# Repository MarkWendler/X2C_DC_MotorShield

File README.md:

# X2C_DC_MotorShield
DC motor driver expansion board for X2C+ development board. [Hardware project]

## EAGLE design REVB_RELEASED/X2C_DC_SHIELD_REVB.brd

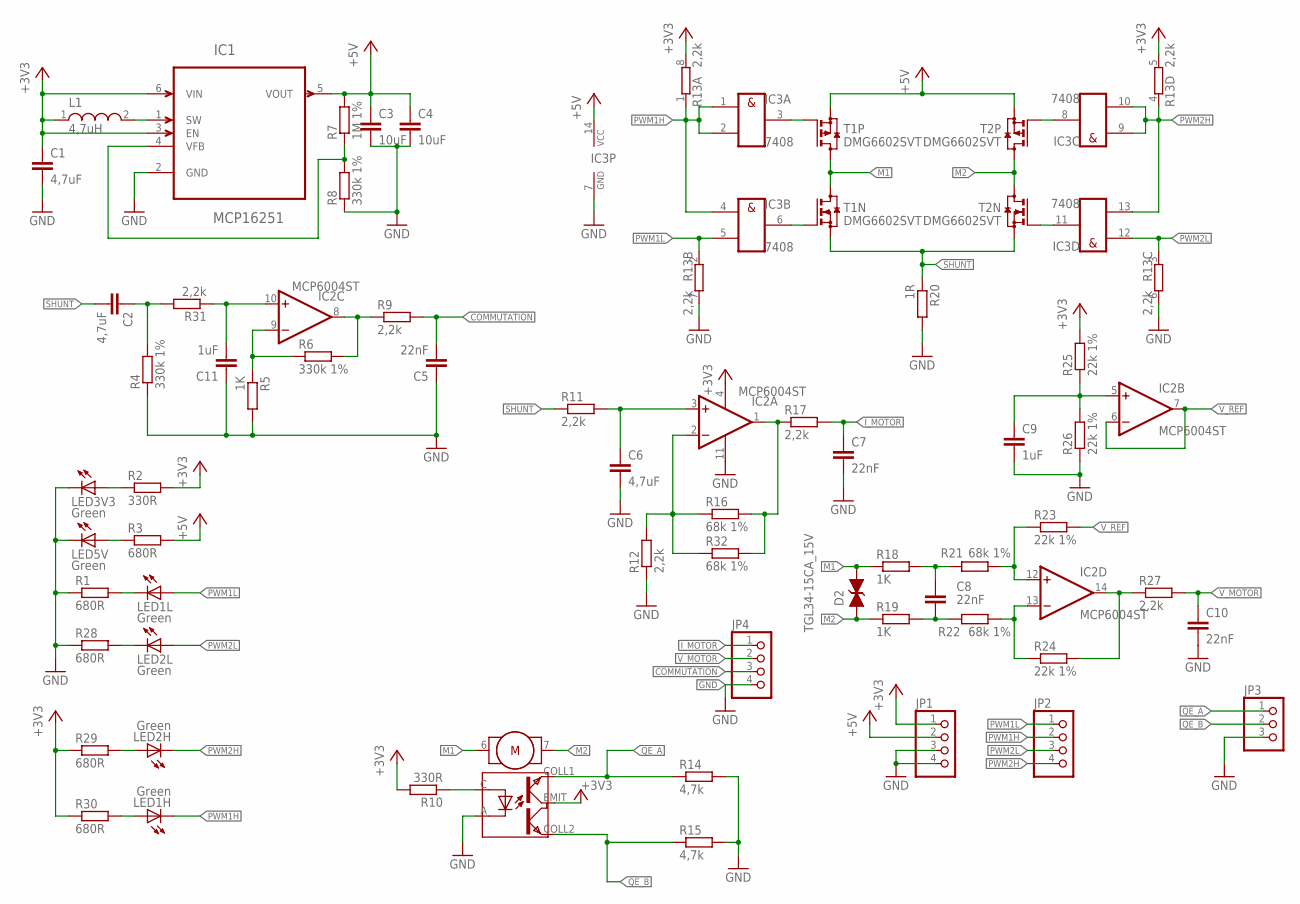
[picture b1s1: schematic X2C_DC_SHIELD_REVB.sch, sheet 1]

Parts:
C1, C2, C6: 4,7uF; C0603K
C3, C4: 10uF; C0805K
C5, C7, C8, C10: 22nF; C0603K
C9, C11: 1uF; C0603K
D2: TGL34-15CA_15V; DO213AA
IC1: MCP16251; SOT95P270X145-6N
IC2: MCP6004ST; TSSOP14
IC3: 7408; TSSOP14
JP1, JP2, JP4: PINHD-1X4; 1X04
JP3: PINHD-1X03_2.54; 1X03
L1: 4,7uH; WE-TPC_3816
LED1H, LED1L, LED2H, LED2L, LED3V3, LED5V: Green; CHIPLED_0805
MOT1: DC_MOT; DC_MOTOR
R1, R3, R28, R29, R30: 680R; R0603
R2, R10: 330R; R0603
R4, R6, R8: 330k 1%; R0603
R5, R18, R19: 1K; R0603
R7: 1M 1%; R0603
R9, R11, R12, R17, R27, R31: 2,2k; R0603
R13: 2,2k; EXBV8V_A
R14, R15: 4,7k; R0603
R16, R21, R22, R32: 68k 1%; R0603
R20: 1R; R0805
R23, R24, R25, R26: 22k 1%; R0603
T1, T2: DMG6602SVT; TSOT23-6

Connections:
+3V3: C1.1, IC1.3 (EN), IC1.6 (VIN), IC2.4 (V+), JP1.1, L1.1, MOT1.EMIT, R2.2, R10.2, R13.5 (2), R13.8 (2), R25.2, R29.1, R30.1; also elsewhere on the board
+5V: C3.1, C4.1, IC1.5 (VOUT), IC3.14 (VCC), JP1.2, R3.2, R7.2, T1.2 (S), T2.2 (S)
COMMUTATION: C5.2, JP4.3, R9.2; also elsewhere on the board
GND: C1.2, C3.2, C4.2, C5.1, C6.2, C7.2, C9.2, C10.2, C11.1, IC1.2 (GND), IC2.11 (V-), IC3.7 (GND), JP1.3, JP1.4, JP3.3, JP4.4, LED3V3.C, LED5V.C, MOT1.A (C), R1.1, R4.1, R5.2, R8.1, R12.1, R13.6 (2), R13.7 (2), R14.2, R15.2, R20.2, R26.1, R28.1; also elsewhere on the board
IMOTOR: IC2.1 (OUT), R16.2, R17.1, R32.2
I_MOTOR: C7.1, JP4.1, R17.2; also elsewhere on the board
M1: D2.C, MOT1.6 (MOT1), R18.1, T1.4 (D), T1.6 (D)
M2: D2.A, MOT1.7 (MOT2), R19.1, T2.4 (D), T2.6 (D)
unnamed: IC3.8 (O), T2.3 (G)
unnamed: IC3.6 (O), T1.1 (G)
unnamed: IC3.3 (O), T1.3 (G)
unnamed: IC1.1 (SW), L1.2
unnamed: C9.1, IC2.5 (+IN), R25.1, R26.2
unnamed: LED2H.A, R29.2
unnamed: IC3.11 (O), T2.1 (G)
unnamed: LED3V3.A, R2.1
unnamed: LED5V.A, R3.1
unnamed: LED1L.C, R1.2
unnamed: IC1.4 (VFB), R7.1, R8.2
unnamed: LED1H.A, R30.2
unnamed: LED2L.C, R28.2
unnamed: IC2.2 (-IN), R12.2, R16.1, R32.1
unnamed: C2.1, R4.2, R31.2
unnamed: IC2.12 (+IN), R21.2, R23.1
unnamed: C8.1, R18.2, R21.1
unnamed: C8.2, R19.2, R22.1
unnamed: IC2.13 (-IN), R22.2, R24.1
unnamed: C6.1, IC2.3 (+IN), R11.2
unnamed: IC2.8 (OUT), R6.2, R9.1
unnamed: IC2.9 (-IN), R5.1, R6.1
unnamed: IC2.14 (OUT), R24.2, R27.1
unnamed: C11.2, IC2.10 (+IN), R31.1
unnamed: MOT1.C (A), R10.1
PWM1H: IC3.1 (I0), IC3.2 (I1), IC3.4 (I0), JP2.2, LED1H.C, R13.1; also elsewhere on the board
PWM1L: IC3.5 (I1), JP2.1, LED1L.A, R13.2 (1); also elsewhere on the board
PWM2H: IC3.9 (I0), IC3.10 (I1), IC3.13 (I1), JP2.4, LED2H.C, R13.4 (1); also elsewhere on the board
PWM2L: IC3.12 (I0), JP2.3, LED2L.A, R13.3 (1); also elsewhere on the board
QE_A: JP3.1, MOT1.COLL1 (COL1), R14.1; also elsewhere on the board
QE_B: JP3.2, MOT1.COLL2 (COL2), R15.1; also elsewhere on the board
SHUNT: C2.2, R11.1, R20.1, T1.5 (S), T2.5 (S)
V_MOTOR: C10.1, JP4.2, R27.2; also elsewhere on the board
V_REF: IC2.6 (-IN), IC2.7 (OUT), R23.2

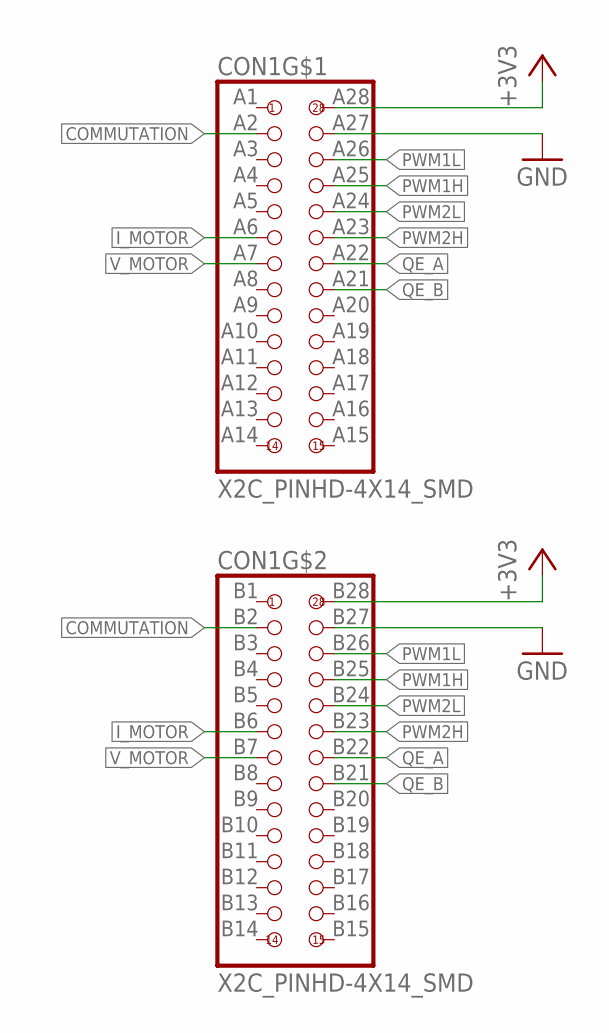
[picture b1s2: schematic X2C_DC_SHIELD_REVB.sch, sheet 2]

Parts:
CON1: X2C_PINHD-4X14_SMD; X2C_4X14_SMD

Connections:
+3V3: CON1.A28, CON1.B28 (A28); also elsewhere on the board
COMMUTATION: CON1.A2, CON1.B2 (A2); also elsewhere on the board
GND: CON1.A27, CON1.B27 (A27); also elsewhere on the board
I_MOTOR: CON1.A6, CON1.B6 (A6); also elsewhere on the board
PWM1H: CON1.A25, CON1.B25 (A25); also elsewhere on the board
PWM1L: CON1.A26, CON1.B26 (A26); also elsewhere on the board
PWM2H: CON1.A23, CON1.B23 (A23); also elsewhere on the board
PWM2L: CON1.A24, CON1.B24 (A24); also elsewhere on the board
QE_A: CON1.A22, CON1.B22 (A22); also elsewhere on the board
QE_B: CON1.A21, CON1.B21 (A21); also elsewhere on the board
V_MOTOR: CON1.A7, CON1.B7 (A7); also elsewhere on the board

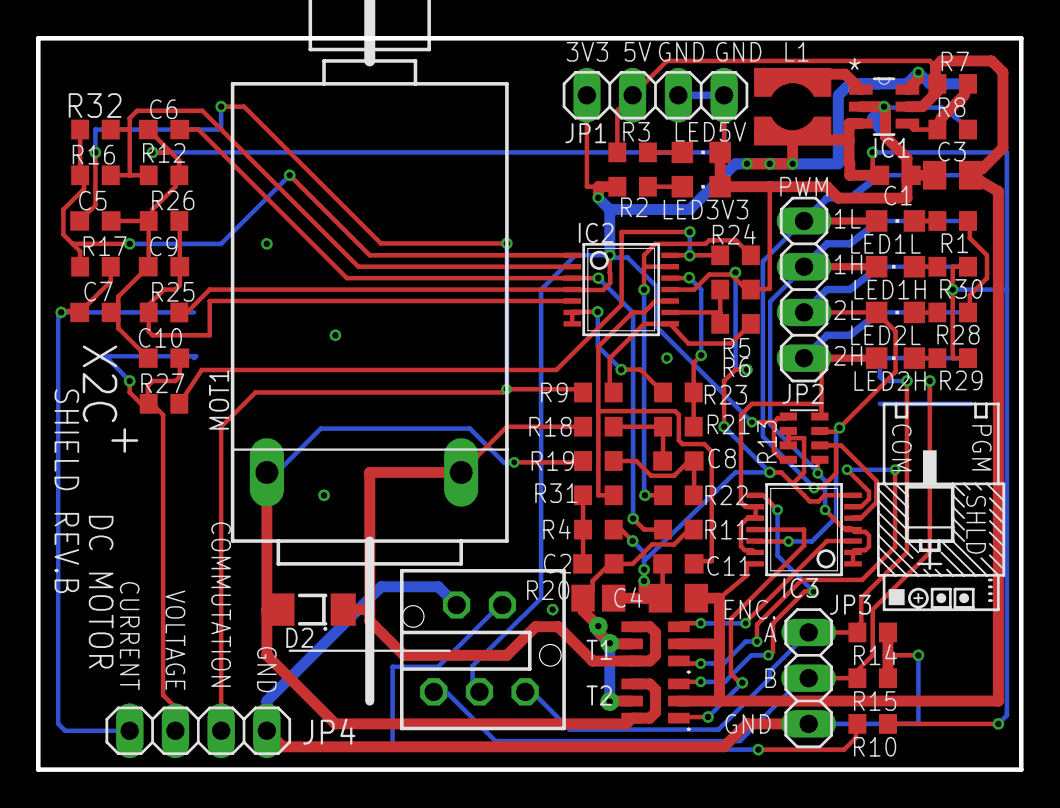
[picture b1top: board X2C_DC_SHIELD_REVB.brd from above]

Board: 2 copper layers, 54.6 x 40.6 mm, 63 parts (1 on the bottom side), 42 nets.

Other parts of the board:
U$1: CE_KUKA+MADE+NAME

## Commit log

2018-08-02 REVA Release
2018-08-02 REVA board and schematics drawing
2018-08-02 REVB_Released version
2018-08-02 Updated amplifier values
2018-08-03 update gitignore to upload mplab projects
2018-08-03 MPLAB X projects added
